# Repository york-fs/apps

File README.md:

# Accelerator Pedal Position Sensor (APPS)

A custom accelerator pedal position sensor built around an STM32F103 MCU for drive-by-wire and EV applications.  
This module measures pedal position using two SS49E Hall-effect sensors with independent, opposed magnets, provides a digital brake signal, and communicates throttle data directly to the inverter over CAN bus.

## Features
- **MCU**: STM32F103
- **Position sensing**:  
  - Two SS49E Hall-effect sensors  
  - Independent, opposed magnet configuration for rule compliance and redundancy 
- **Brake output**: Digital output line for brake LED / ECU input  
- **User controls**:  
  - Reset button  
  - Calibration button (pedal travel limits)
- **CAN transceiver**:  
  - Throttle data transmission  
  - Ready-to-drive state reporting  
  - Calibration / curve configuration

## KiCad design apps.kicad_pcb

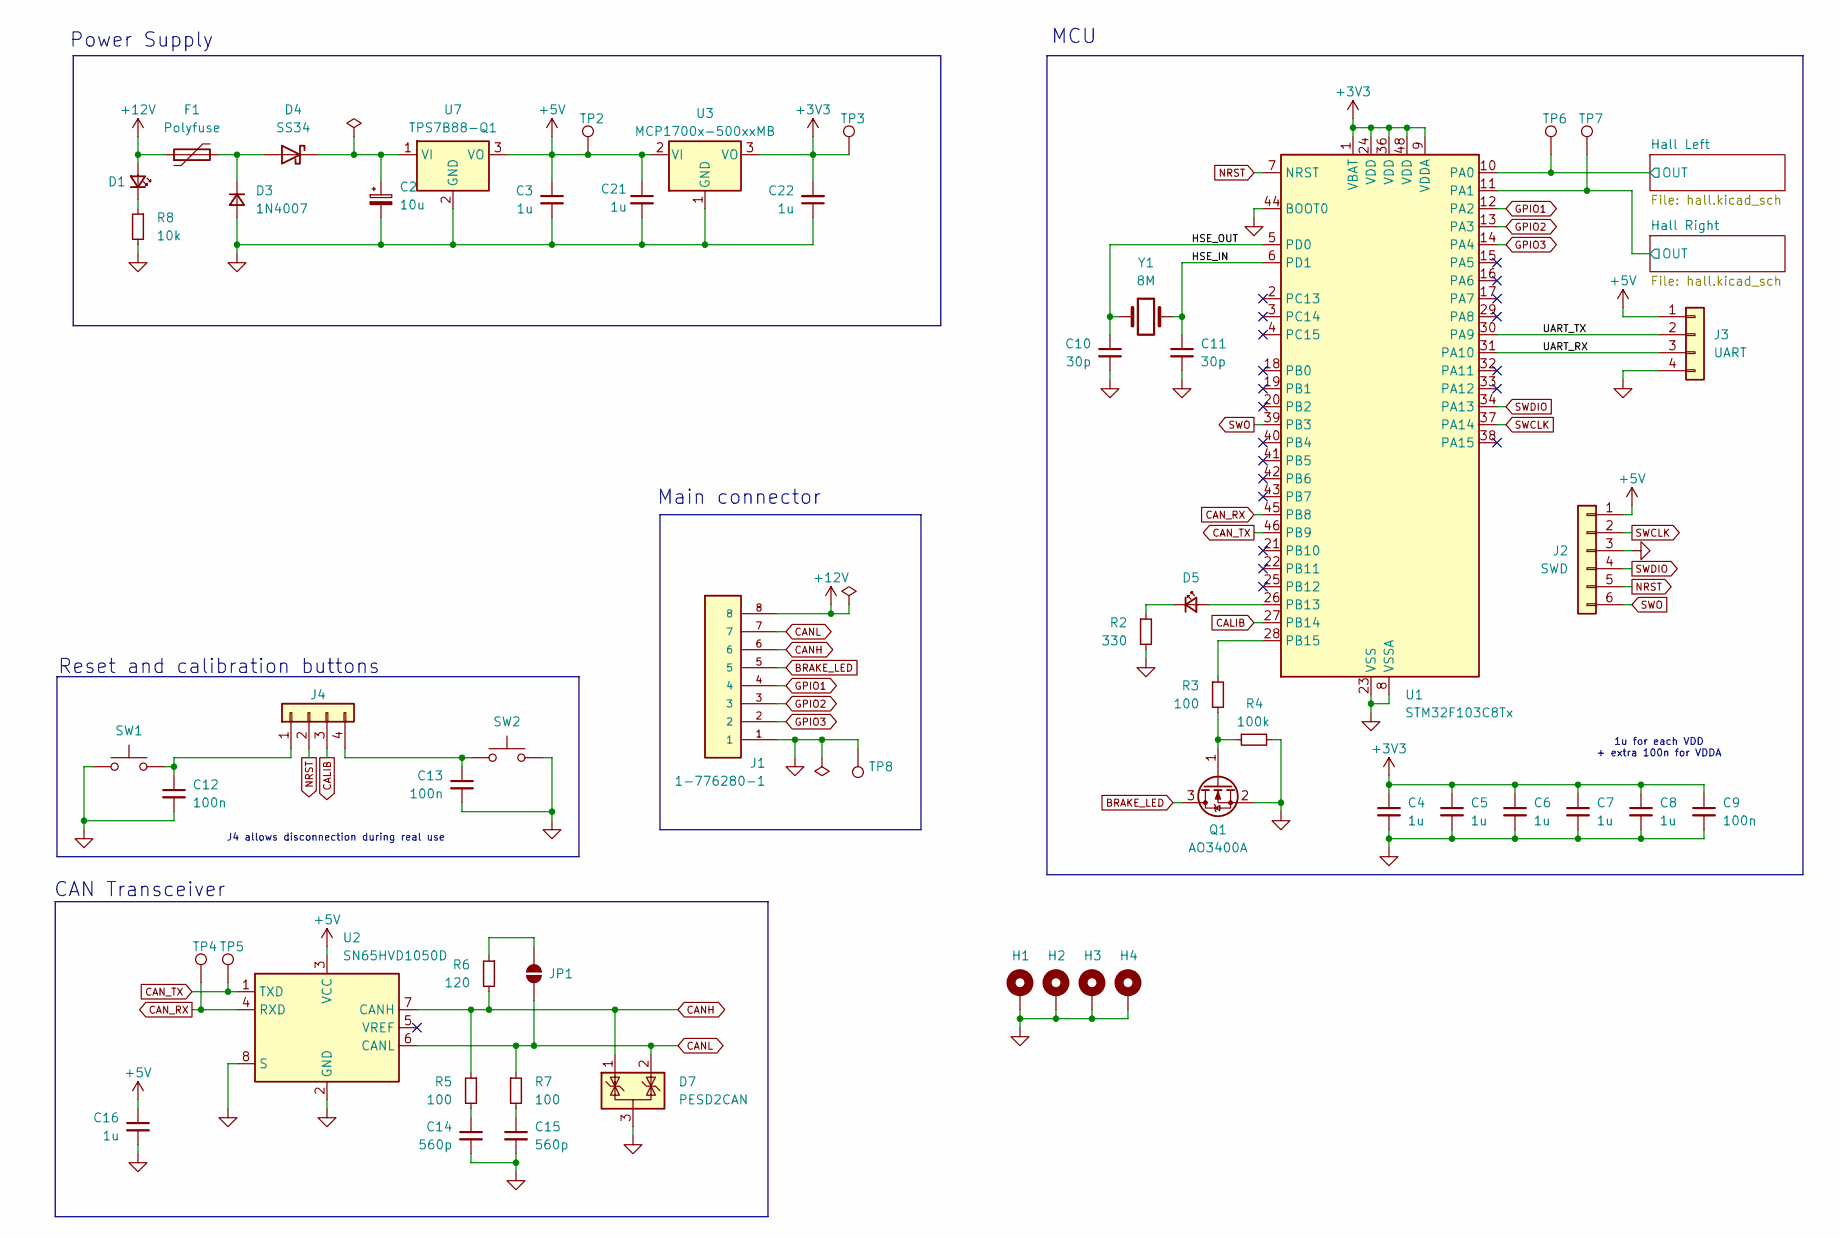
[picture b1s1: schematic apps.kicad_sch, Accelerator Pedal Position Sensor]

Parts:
C2: 10u; CP_Elec_6.3x5.4
C3, C4, C5, C6, C7, C8, C16, C21, C22: 1u; C_0603_1608Metric
C9, C12, C13: 100n; C_0603_1608Metric
C10, C11: 30p; C_0603_1608Metric
C14, C15: 560p; C_0603_1608Metric
D1, D5: LED_Small; LED_0603_1608Metric
D3: 1N4007; D_SOD-123F
D4: SS34; D_SMA
D7: PESD2CAN; SOT-23
F1: Polyfuse; R_0805_2012Metric
H1, H2, H3, H4: MountingHole_Pad; MountingHole_3.2mm_M3_Pad_Via
J1: 1-776280-1; TE_1-776280-1; PARTREV F8
J2: SWD; PinHeader_1x06_P2.54mm_Vertical
J3: UART; PinHeader_1x04_P2.54mm_Vertical
J4: Conn_01x04; PinHeader_1x04_P2.54mm_Vertical
JP1: SolderJumper_2_Open; SolderJumper-2_P1.3mm_Open_RoundedPad1.0x1.5mm
Q1: AO3400A; SOT-23
R2: 330; R_0603_1608Metric
R3, R5, R7: 100; R_0603_1608Metric
R4: 100k; R_0603_1608Metric
R6: 120; R_0603_1608Metric
R8: 10k; R_0603_1608Metric
SW1, SW2: SW_Push; SW_Push_SPST_NO_Alps_SKRK
TP2, TP3, TP4, TP5, TP6, TP7, TP8: TestPoint; TestPoint_Keystone_5000-5004_Miniature
U1: STM32F103C8Tx; LQFP-48_7x7mm_P0.5mm
U2: SN65HVD1050D; SOIC-8_3.9x4.9mm_P1.27mm
U3: MCP1700x-500xxMB; SOT-89-3
U7: TPS7B88-Q1; TO-252-2
Y1: 8M; Crystal_SMD_5032-2Pin_5.0x3.2mm

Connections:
+3V3: C4.1, C5.1, C6.1, C7.1, C8.1, C9.1, C22.2, TP3.1, U1.1 (VBAT), U1.9 (VDDA), U1.24 (VDD), U1.36 (VDD), U1.48 (VDD), U3.3 (VO); also elsewhere on the board
+5V: C3.1, C16.1, C21.1, J2.1, J3.1, TP2.1, U2.3 (VCC), U3.2 (VI), U7.3 (VO)
+12V: D1.2 (A), F1.1, J1.8
/HSE_IN: C11.1, U1.6 (PD1), Y1.2
/HSE_OUT: C10.1, U1.5 (PD0), Y1.1
/Hall Left/OUT: TP6.1, U1.10 (PA0); also elsewhere on the board
/Hall Right/OUT: TP7.1, U1.11 (PA1); also elsewhere on the board
/UART_RX: J3.3, U1.31 (PA10)
/UART_TX: J3.2, U1.30 (PA9)
BRAKE_LED: J1.5, Q1.3 (D)
CALIB: J4.3, U1.27 (PB14)
CANH: D7.1 (K), J1.6, R5.1, R6.2, U2.7 (CANH)
CANL: D7.2 (K), J1.7, JP1.2 (B), R7.1, U2.6 (CANL)
CAN_RX: TP4.1, U1.45 (PB8), U2.4 (RXD)
CAN_TX: TP5.1, U1.46 (PB9), U2.1 (TXD)
GND: C2.2, C3.2, C4.2, C5.2, C6.2, C7.2, C8.2, C9.2, C10.2, C11.2, C12.2, C13.2, C14.2, C15.2, C16.2, C21.2, C22.1, D3.2 (A), D7.3 (A), H1.1, H2.1, H3.1, H4.1, J1.1, J2.3, J3.4, Q1.2 (S), R2.2, R4.2, R8.2, SW1.1, SW2.1, TP8.1, U1.8 (VSSA), U1.23 (VSS), U1.35 (VSS), U1.44 (BOOT0), U1.47 (VSS), U2.2 (GND), U2.8 (S), U3.1 (GND), U7.2 (GND); also elsewhere on the board
GPIO1: J1.4, U1.12 (PA2)
GPIO2: J1.3, U1.13 (PA3)
GPIO3: J1.2, U1.14 (PA4)
NRST: J2.5, J4.2, U1.7 (NRST)
unnamed: C14.1, R5.2
unnamed: C15.1, R7.2
unnamed: D1.1 (K), R8.1
unnamed: D3.1 (K), D4.2 (A), F1.2
unnamed: C2.1, D4.1 (K), U7.1 (VI)
unnamed: D5.2 (A), U1.26 (PB13)
unnamed: D5.1 (K), R2.1
unnamed: C12.1, J4.1, SW1.2
unnamed: C13.1, J4.4, SW2.2
unnamed: JP1.1 (A), R6.1
unnamed: Q1.1 (G), R3.2, R4.1
unnamed: R3.1, U1.28 (PB15)
SWCLK: J2.2, U1.37 (PA14)
SWDIO: J2.4, U1.34 (PA13)
SWO: J2.6, U1.39 (PB3)

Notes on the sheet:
Power Supply
MCU
Reset and calibration buttons
1u for each VDD + extra 100n for VDDA
J4 allows disconnection during real use
CAN Transceiver
Main connector

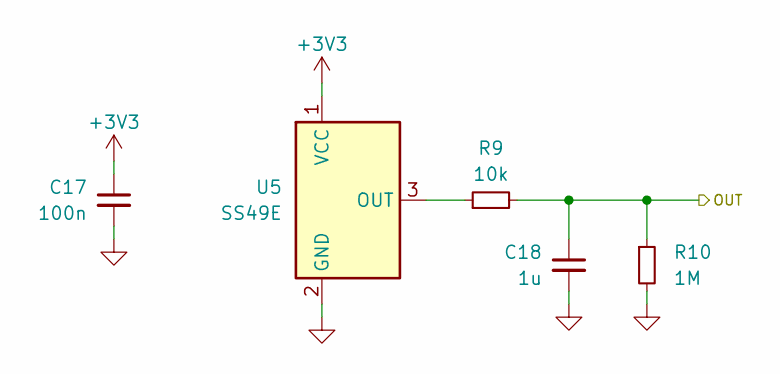
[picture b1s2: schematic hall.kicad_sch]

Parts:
C17: 100n; C_0603_1608Metric
C18: 1u; C_0603_1608Metric
R9: 10k; R_0603_1608Metric
R10: 1M; R_0603_1608Metric
U5: SS49E; SS49E_TO_92_Inline

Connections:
+3V3: C17.1, U5.1 (VCC); also elsewhere on the board
/Hall Left/OUT: C18.1, R9.2, R10.1; also elsewhere on the board
GND: C17.2, C18.2, R10.2, U5.2 (GND); also elsewhere on the board
unnamed: R9.1, U5.3 (OUT)

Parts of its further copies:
C19: 100n; C_0603_1608Metric
C20: 1u; C_0603_1608Metric
R11: 10k; R_0603_1608Metric
R12: 1M; R_0603_1608Metric
U6: SS49E; SS49E_TO_92_Inline

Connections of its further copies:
+3V3: C19.1, U6.1 (VCC); also elsewhere on the board
/Hall Right/OUT: C20.1, R11.2, R12.1; also elsewhere on the board
GND: C19.2, C20.2, R12.2, U6.2 (GND); also elsewhere on the board
unnamed: R11.1, U6.3 (OUT)

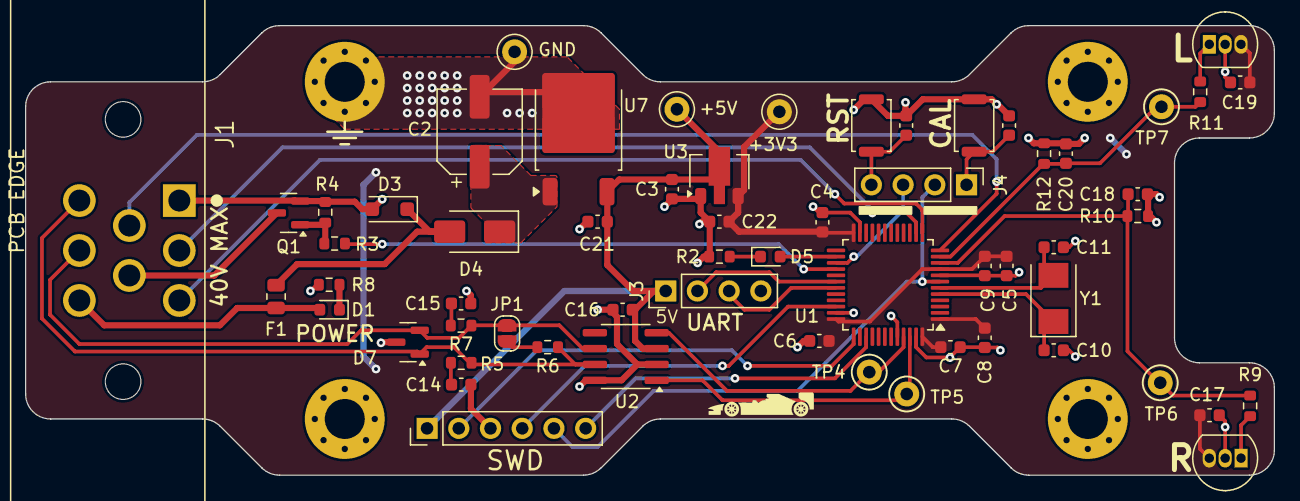
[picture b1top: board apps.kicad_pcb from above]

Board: 2 copper layers, 100.0 x 36.0 mm, 64 parts (0 on the bottom side), 37 nets.

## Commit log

2025-01-30 schematic: Move C2 after D3
2025-01-30 schematic: Add another ESD TVS diode to 12V input
2025-01-31 schematic: Fix revision
2025-01-31 schematic: Some changes
    * Add test points for hall sensors
    * Assign 2.54 mm header footprints
    * Fix CAN termination resistor
2025-01-31 schematic: Add ESD TVS diodes for CAN bus
2025-01-31 schematic: Assign footprints for 12 V diodes
2025-02-03 meta: Add backup directory to gitignore
2025-02-03 schematic: Add symbol and footprint for main connector
2025-02-03 pcb: Create first PCB revision
2025-03-31 Changed SS49E footprint and updated to KiCAD 9
2025-03-31 Updated CAN Transceiver and LDO
2025-09-24 Added image
2025-11-22 meta: Update gitignore
2025-11-22 meta: Set LF line endings explicitly
